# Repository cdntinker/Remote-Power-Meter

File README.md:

## The Jacks
* J1 Power / Communications
* J2 Source connection for USB
* J3 Source connection for whatever
* J4 Source connection for whatever
* J5 Load connection for USB
* J6 Load connection for whatever
* J7 Load connection for whatever
* Disp1 Little OLED screen

## JP1 & JP2
These allow 4 of the possible 16 addresses for the INA219 chip.

The chip allows for 16 addresses by tying A0 & A1 to GND, VS+, SCL & SDA is various conbinations but I don't feel that much chaos is warranted in this case.

## R1 & R2
These are the shunt resistor that the INA219 uses for measuring current. There are 2 resistors in parallel to improve power handling (& possibly accuracy). 

A 2816 SMD resistor can typically handle ~2W and the initial design incentive is a device capable of supplying 4W.

## The LEDs
D1 is for indicating connection status.

D2 is intended to show alerts & such at a glance.

JP3 is just there to allow for driving the LEDs from either raw 5v (from the USB supply) or 3v3 (from the regulator).

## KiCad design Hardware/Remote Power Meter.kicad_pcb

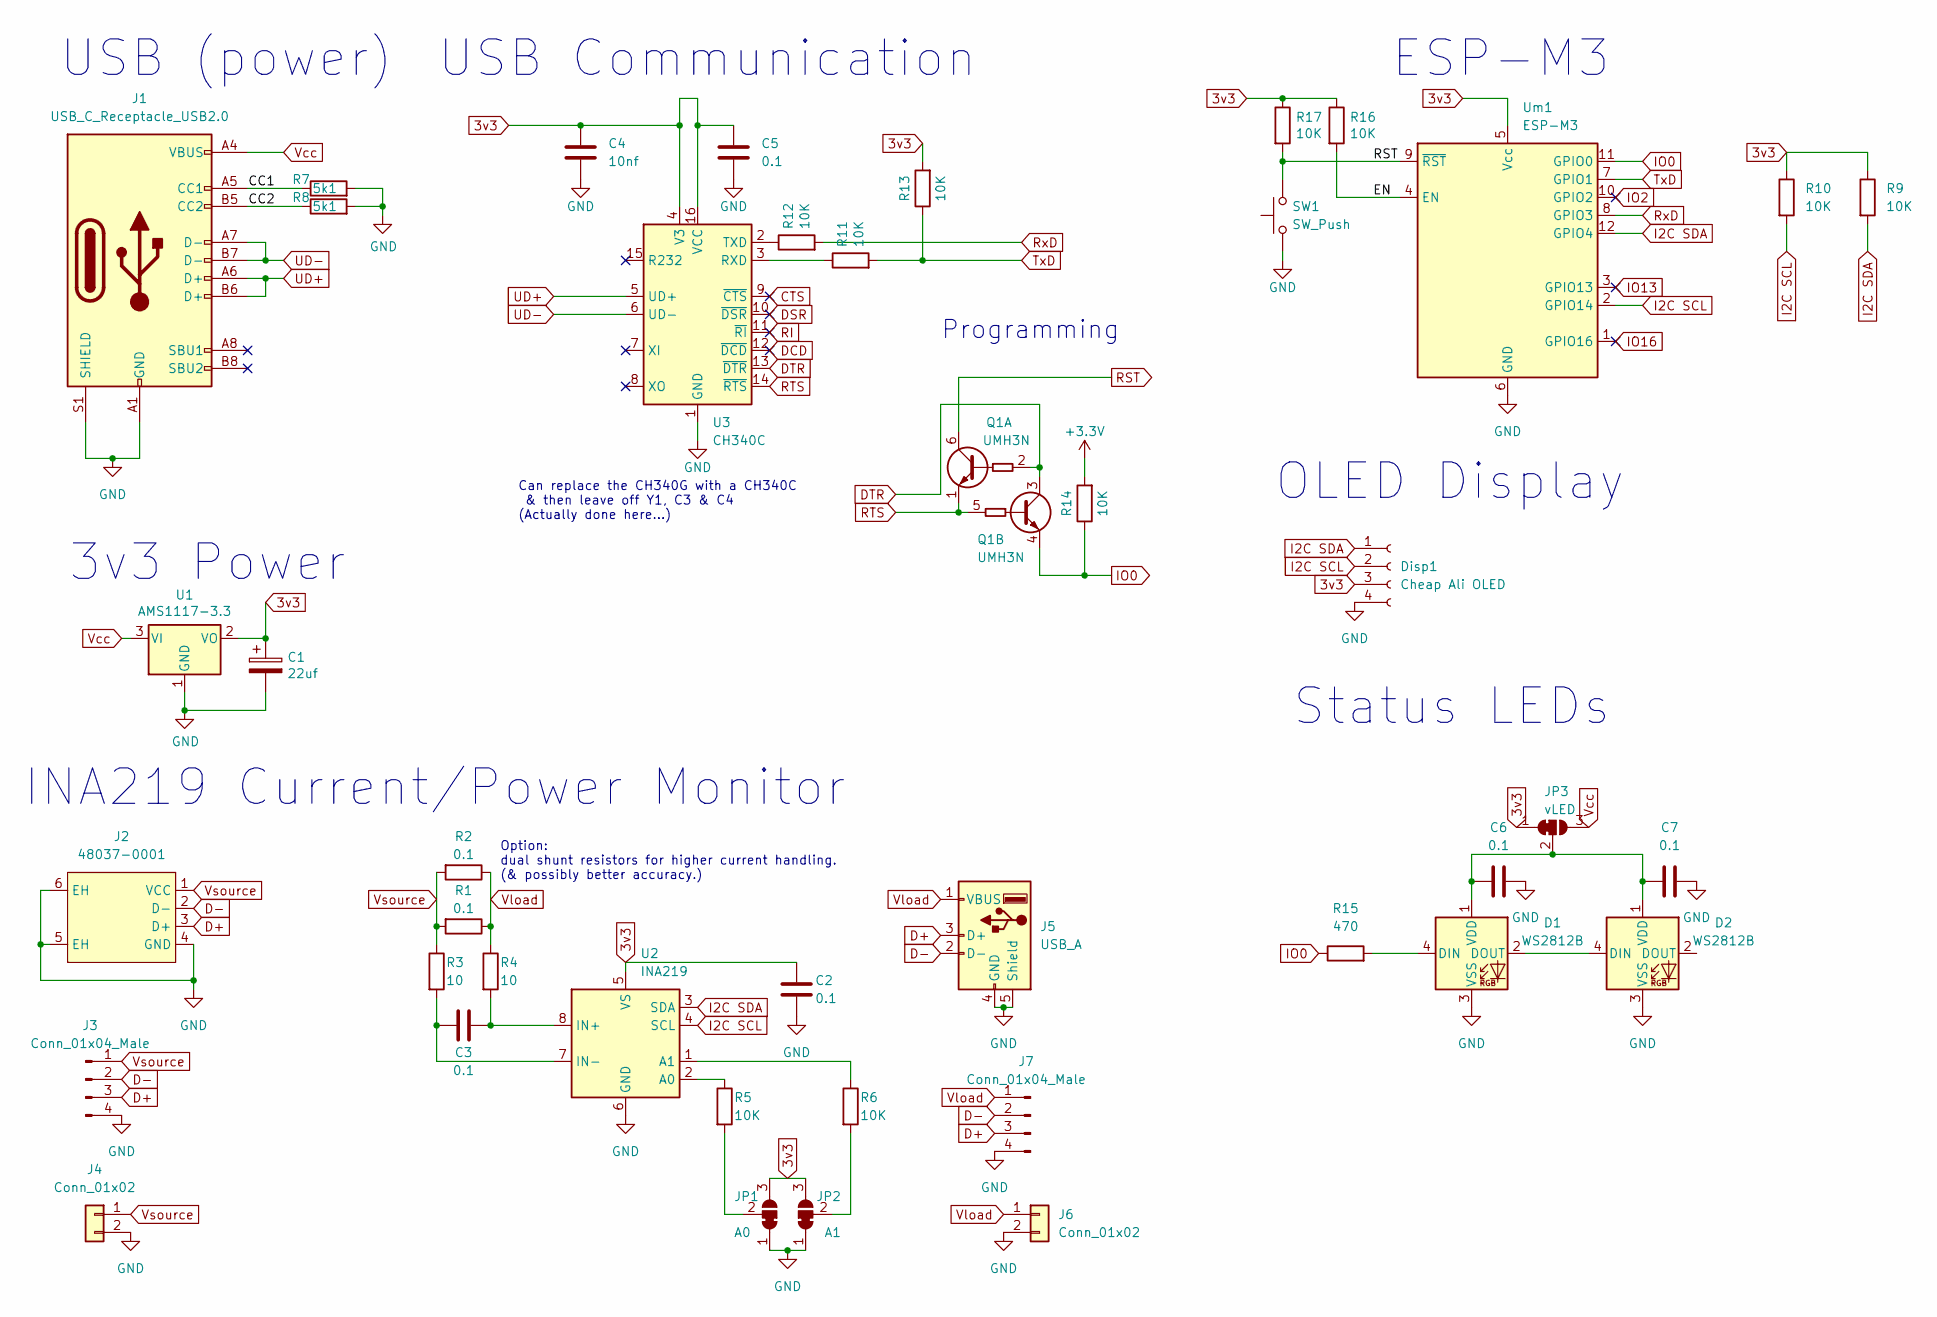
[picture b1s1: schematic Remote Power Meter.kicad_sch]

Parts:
C1: 22uf; CP_EIA-6032-28_Kemet-C_Pad2.25x2.35mm_HandSolder; LCSC C145122
C2, C3, C5, C6, C7: 0.1; C_0603_1608Metric_Pad1.08x0.95mm_HandSolder; LCSC C14663
C4: 10nf; C_0603_1608Metric_Pad1.08x0.95mm_HandSolder; LCSC C161232
D1, D2: WS2812B; LED_WS2812B_PLCC4_5.0x5.0mm_P3.2mm; LCSC C2843785
Disp1: Cheap Ali OLED; PinSocket_1x04_P2.54mm_Vertical
J1: USB_C_Receptacle_USB2.0; USB_C_Receptacle_HRO_TYPE-C-31-M-12; LCSC C2765186
J2: 48037-0001; USB-A-TH_48037-0001; LCSC C136455
J3, J7: Conn_01x04_Male; PinHeader_1x04_P2.54mm_Vertical
J4, J6: Conn_01x02; TerminalBlock_4Ucon_1x02_P3.50mm_Horizontal; LCSC C784940
J5: USB_A; USB_A_CONNFLY_DS1095-WNR0; LCSC C6389922
JP1: A0; SolderJumper-3_P1.3mm_Bridged12_RoundedPad1.0x1.5mm
JP2: A1; SolderJumper-3_P1.3mm_Bridged12_RoundedPad1.0x1.5mm
JP3: vLED; SolderJumper-3_P1.3mm_Bridged12_RoundedPad1.0x1.5mm
Q1: UMH3N; SOT-363_SC-70-6; LCSC C62892
R1, R2: 0.1; R_2816_7142Metric_Pad3.20x4.45mm_HandSolder; LCSC C844084
R3, R4: 10; R_0603_1608Metric_Pad0.98x0.95mm_HandSolder; LCSC C22859
R5, R6, R9, R10: 10K; R_0603_1608Metric_Pad0.98x0.95mm_HandSolder
R7, R8: 5k1; R_0603_1608Metric_Pad0.98x0.95mm_HandSolder; LCSC C23203
R11, R12, R13, R14, R16, R17: 10K; R_0603_1608Metric_Pad0.98x0.95mm_HandSolder; LCSC C25804
R15: 470; R_0603_1608Metric_Pad0.98x0.95mm_HandSolder; LCSC C114669
SW1: SW_Push; SW_Push_TS273014TP; LCSC C2858276
U1: AMS1117-3.3; SOT-223-3_TabPin2; LCSC C347256
U2: INA219; SOIC-8_3.9x4.9mm_P1.27mm; LCSC C138706
U3: CH340C; SOIC-16_3.9x9.9mm_P1.27mm; LCSC C84681
Um1: ESP-M3; LCSC C19949058

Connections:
3v3: C1.1, C2.1, C4.1, C5.2, Disp1.3, JP1.3 (B), JP2.3 (B), JP3.1 (A), R9.1, R10.1, R13.2, R16.1, R17.1, U1.2 (VO), U2.5 (VS), U3.4 (V3), U3.16 (VCC), Um1.5 (Vcc)
+3V3: R14.2
/CC1: J1.A5 (CC1), R7.1
/CC2: J1.B5 (CC2), R8.1
/EN: R16.2, Um1.4 (EN)
CTS: U3.9 (~CTS)
D+: J2.3 (D+), J3.3, J5.3 (D+), J7.3
D-: J2.2 (D-), J3.2, J5.2 (D-), J7.2
DCD: U3.12 (~DCD)
DSR: U3.10 (~DSR)
DTR: Q1.2 (B1), Q1.3 (C2), U3.13 (~DTR)
GND: C1.2, C2.2, C4.2, C5.1, C6.2, C7.2, D1.3 (VSS), D2.3 (VSS), Disp1.4, J1.A1 (GND), J1.A12 (GND), J1.B1 (GND), J1.B12 (GND), J1.S1 (SHIELD), J2.4 (GND), J2.5 (EH), J2.6 (EH), J3.4, J4.2, J5.4 (GND), J5.5 (Shield), J6.2, J7.4, JP1.1 (A), JP2.1 (A), R7.2, R8.2, SW1.1, U1.1 (GND), U2.6 (GND), U3.1 (GND), Um1.6 (GND)
I2C SCL: Disp1.2, R10.2, U2.4 (SCL), Um1.2 (GPIO14)
I2C SDA: Disp1.1, R9.2, U2.3 (SDA), Um1.12 (GPIO4)
IO0: Q1.4 (E2), R14.1, R15.1, Um1.11 (GPIO0)
IO2: Um1.10 (GPIO2)
IO13: Um1.3 (GPIO13)
IO16: Um1.1 (GPIO16)
unnamed: C3.1, R4.2, U2.8 (IN+)
unnamed: C3.2, R3.2, U2.7 (IN-)
unnamed: C6.1, C7.1, D1.1 (VDD), D2.1 (VDD), JP3.2 (C)
unnamed: D1.2 (DOUT), D2.4 (DIN)
unnamed: D1.4 (DIN), R15.2
unnamed: JP1.2 (C), R5.2
unnamed: JP2.2 (C), R6.2
unnamed: R5.1, U2.2 (A0)
unnamed: R6.1, U2.1 (A1)
unnamed: R11.1, U3.3 (RXD)
unnamed: R12.1, U3.2 (TXD)
RI: U3.11 (~RI)
RST: Q1.6 (C1), R17.2, SW1.2, Um1.9 (~RST)
RTS: Q1.1 (E1), Q1.5 (B2), U3.14 (~RTS)
RxD: R12.2, Um1.8 (GPIO3)
TxD: R11.2, R13.1, Um1.7 (GPIO1)
UD+: J1.A6 (D+), J1.B6 (D+), U3.5 (UD+)
UD-: J1.A7 (D-), J1.B7 (D-), U3.6 (UD-)
Vcc: J1.A4 (VBUS), J1.A9 (VBUS), J1.B4 (VBUS), J1.B9 (VBUS), JP3.3 (B), U1.3 (VI)
Vload: J5.1 (VBUS), J6.1, J7.1, R1.1, R2.1, R4.1
Vsource: J2.1 (VCC), J3.1, J4.1, R1.2, R2.2, R3.1

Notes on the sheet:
OLED Display
Status LEDs
Programming
ESP-M3
USB (power)
3v3 Power
Can replace the CH340G with a CH340C & then leave off Y1, C3 & C4 (Actually done here...)
USB Communication
Option: dual shunt resistors for higher current handling. (& possibly better accuracy.)
INA219 Current/Power Monitor

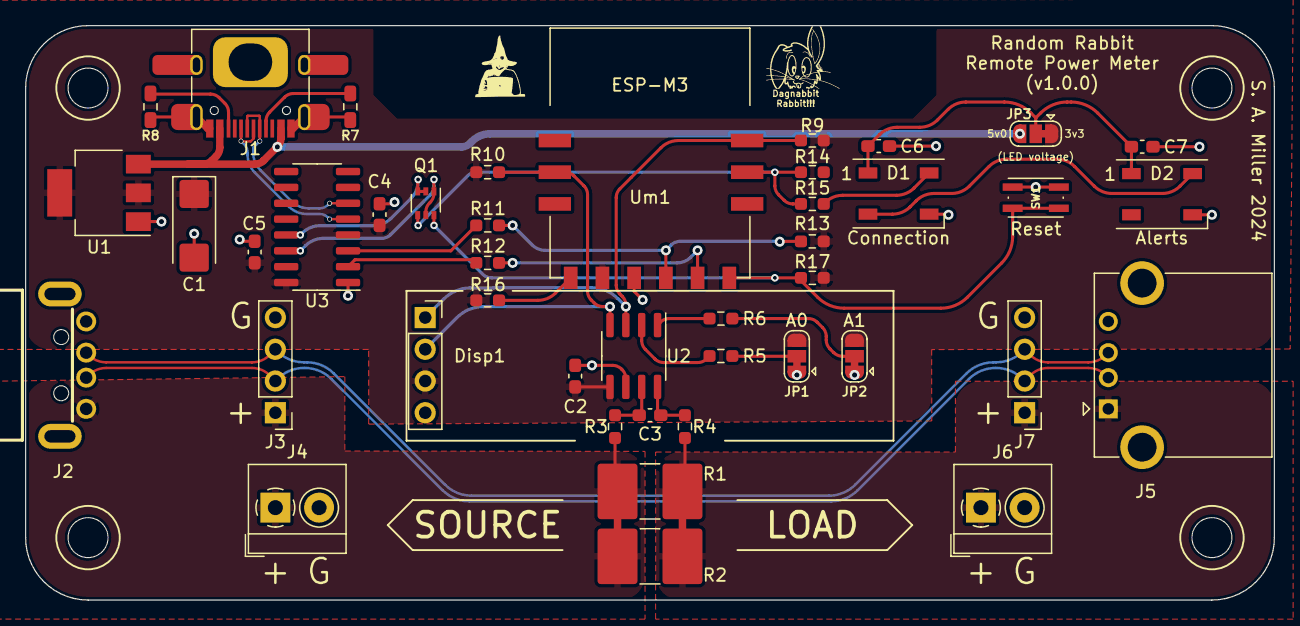
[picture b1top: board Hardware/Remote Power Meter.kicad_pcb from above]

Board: 2 copper layers, 100.0 x 46.0 mm, 43 parts (0 on the bottom side), 31 nets.

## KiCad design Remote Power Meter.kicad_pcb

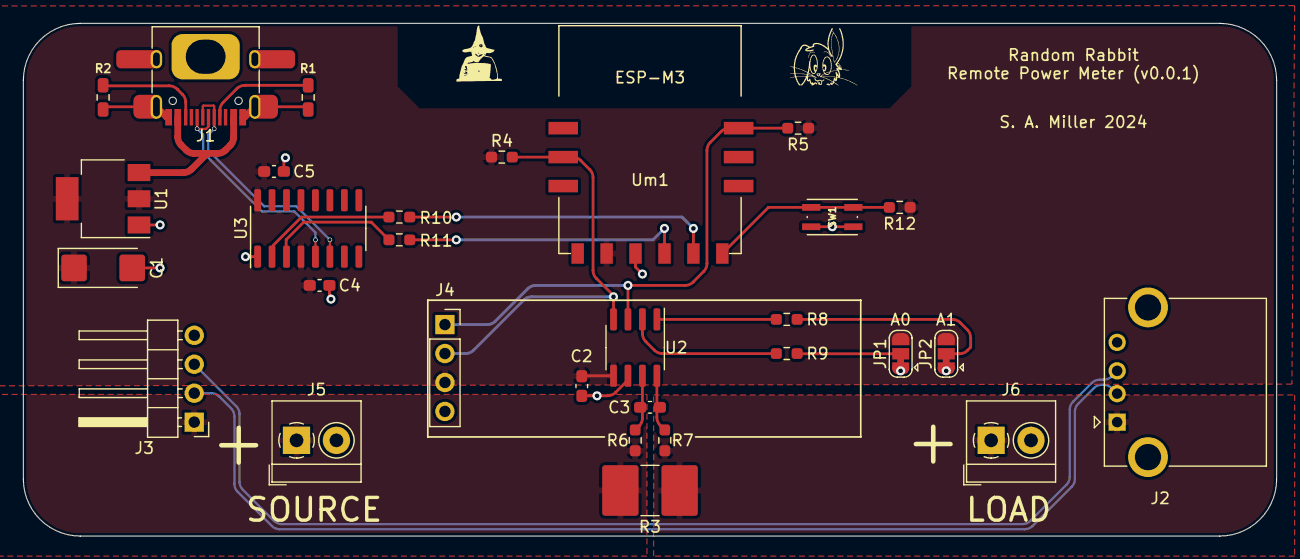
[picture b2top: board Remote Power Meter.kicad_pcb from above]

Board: 2 copper layers, 110.0 x 45.0 mm, 30 parts (0 on the bottom side), 24 nets.

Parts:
C1: 22uf; CP_EIA-6032-28_Kemet-C_Pad2.25x2.35mm_HandSolder
C2, C3: 0.1; C_0603_1608Metric_Pad1.08x0.95mm_HandSolder
C4: 10nf; C_0603_1608Metric_Pad1.08x0.95mm_HandSolder
C5: 100nf; C_0603_1608Metric_Pad1.08x0.95mm_HandSolder
J1: USB_C_Receptacle_USB2.0; USB_C_Receptacle_HRO_TYPE-C-31-M-12
J2: USB_A; USB_A_CONNFLY_DS1095-WNR0
J3: Conn_01x04_Male; PinHeader_1x04_P2.54mm_Horizontal
J4: Conn_01x04_Female; PinSocket_1x04_P2.54mm_Vertical
J5, J6: Conn_01x02; TerminalBlock_4Ucon_1x02_P3.50mm_Horizontal
JP1: A0; SolderJumper-3_P1.3mm_Bridged12_RoundedPad1.0x1.5mm
JP2: A1; SolderJumper-3_P1.3mm_Bridged12_RoundedPad1.0x1.5mm
R1, R2: 5k1; R_0603_1608Metric_Pad0.98x0.95mm_HandSolder
R3: 0.1; R_2816_7142Metric_Pad3.20x4.45mm_HandSolder
R4, R5, R8, R9, R10, R11, R12: 10K; R_0603_1608Metric_Pad0.98x0.95mm_HandSolder
R6, R7: 10; R_0603_1608Metric_Pad0.98x0.95mm_HandSolder
SW1: SW_Push; SW_Push_TS273014TP
U1: AMS1117-3.3; SOT-223-3_TabPin2
U2: INA219AxD; SOIC-8_3.9x4.9mm_P1.27mm
U3: CH340C; SOIC-16_3.9x9.9mm_P1.27mm
Um1: ESP-M3

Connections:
3v3: C1.1, C2.1, C4.1, C5.1, J4.3, JP1.3 (B), JP2.3 (B), R4.1, R5.1, R12.1, U1.2 (VO), U2.5 (VS), U3.4 (V3), U3.16 (VCC), Um1.5 (Vcc)
/CC1: J1.A5 (CC1), R1.1
/CC2: J1.B5 (CC2), R2.1
/Vload: J2.1 (VBUS), J6.1, R3.1, R7.1
/Vsource: J3.1, J5.1, R3.2, R6.1
D+: J2.3 (D+), J3.3
D-: J2.2 (D-), J3.2
GND: C1.2, C2.2, C4.2, C5.2, J1.A1 (GND), J1.A12 (GND), J1.B1 (GND), J1.B12 (GND), J1.S1 (SHIELD), J2.4 (GND), J2.5 (Shield), J3.4, J4.4, J5.2, J6.2, JP1.1 (A), JP2.1 (A), R1.2, R2.2, SW1.1, U1.1 (GND), U2.6 (GND), U3.1 (GND), Um1.6 (GND)
I2C SCL: J4.2, R4.2, U2.4 (SCL), Um1.2 (GPIO14)
I2C SDA: J4.1, R5.2, U2.3 (SDA), Um1.12 (GPIO4)
unnamed: C3.1, R7.2, U2.8 (IN+)
unnamed: C3.2, R6.2, U2.7 (IN-)
unnamed: JP1.2 (C), R9.2
unnamed: JP2.2 (C), R8.2
unnamed: R8.1, U2.1 (A1)
unnamed: R9.1, U2.2 (A0)
unnamed: R10.1, U3.2 (TXD)
unnamed: R11.1, U3.3 (RXD)
RST: R12.2, SW1.2, Um1.9 (~RST)
RxD: R10.2, Um1.8 (GPIO3)
TxD: R11.2, Um1.7 (GPIO1)
UD+: J1.A6 (D+), J1.B6 (D+), U3.5 (UD+)
UD-: J1.A7 (D-), J1.B7 (D-), U3.6 (UD-)
Vcc: J1.A4 (VBUS), J1.A9 (VBUS), J1.B4 (VBUS), J1.B9 (VBUS), U1.3 (VI)

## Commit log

2024-02-25 Moved hardware into subfolder
2024-02-26 Now programmable via USB
2024-02-26 Possibly reached v1.0.0
2024-02-29 Added LCSC BOM
2024-03-08 bye bye bloody wrl file(s)
2024-03-09 bye bye bloody wrl files
